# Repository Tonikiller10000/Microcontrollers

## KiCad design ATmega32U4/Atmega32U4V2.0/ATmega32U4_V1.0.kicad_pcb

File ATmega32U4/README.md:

# ATmega32U4

### Description:
This is an arduino micro development board with the ATmega32U4 microcontroller witch has integrated USB comunication protocol and don\`t need an external FTDI programmer.
This protothype can be used as an keyboard or an Keystroke injection tool because of it\`s integrated USB comunication protocol witch can very easely be used with the Keyboard.h library in the arduino IDE.

<table>
  <tr>
    <td></td>
    <td></td>
    <td></td>
  </tr>
 </table>

> [!IMPORTANT]
> The board need further testing and documentation. 

Links:
- ATmega32U4 datasheet: https://ww1.microchip.com/downloads/en/DeviceDoc/doc7799.pdf
- Results: https://github.com/Tonikiller10000/ATmega32U4/blob/main/Atmega32u4_Pictures/4.png
- Schematic1: https://static5.arrow.com/pdfs/2013/10/14/2/49/47/170/arduin_/manual/24arduino-micro-schematic.pdf
- Schematic2: https://cdn.sparkfun.com/datasheets/Dev/Arduino/Boards/Pro_Micro_v13b.pdf
- forum: https://forum.arduino.cc/t/my-first-atmega32u4-schematic/886582/3
- helping document: https://cdn-learn.adafruit.com/downloads/pdf/atmega32u4-breakout.pdf
- GitHub: https://github.com/adafruit/Adafruit_Atmega32u4_Breakout_Board

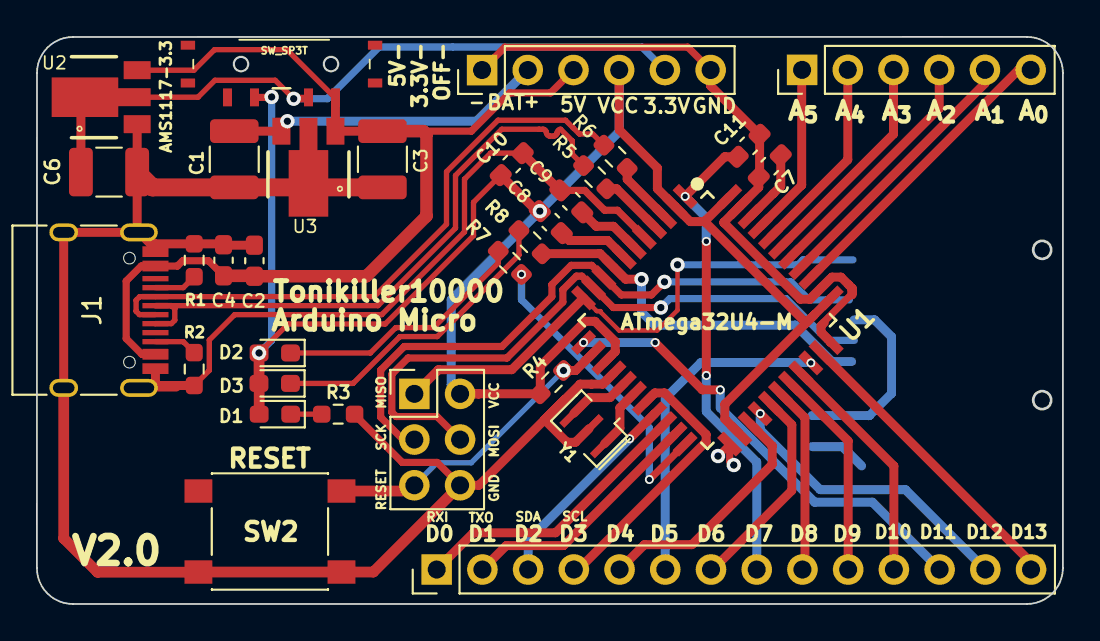
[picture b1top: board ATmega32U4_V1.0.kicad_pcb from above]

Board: 2 copper layers, 57.0 x 31.5 mm, 33 parts (1 on the bottom side), 45 nets.

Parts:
C1, C3: 100uF; C_1210_3225Metric_Pad1.33x2.70mm_HandSolder
C2, C7, C11: 0.1uF; C_0603_1608Metric_Pad1.08x0.95mm_HandSolder
C4: 10uF; C_0603_1608Metric_Pad1.08x0.95mm_HandSolder
C6: 10uF; C_1210_3225Metric_Pad1.33x2.70mm_HandSolder
C8, C9, C10: 1uF; C_0603_1608Metric_Pad1.08x0.95mm_HandSolder
C12: 0.1u; C_0603_1608Metric_Pad1.08x0.95mm_HandSolder
D1: POW; LED_0603_1608Metric_Pad1.05x0.95mm_HandSolder
D2: RX_LED; LED_0603_1608Metric_Pad1.05x0.95mm_HandSolder
D3: TX_LED; LED_0603_1608Metric_Pad1.05x0.95mm_HandSolder
J1: USB-C; USB_C_Receptacle_HRO_TYPE-C-31-M-12
J4: Conn_01x14; PinHeader_1x14_P2.54mm_Vertical
J5: ICSP; PinHeader_2x03_P2.54mm_Vertical
J6, J7: Conn_01x06; PinHeader_1x06_P2.54mm_Vertical
R1, R2: 5K1; R_0603_1608Metric_Pad0.98x0.95mm_HandSolder
R3: 1K; R_0603_1608Metric_Pad0.98x0.95mm_HandSolder
R4: 10K; R_0603_1608Metric_Pad0.98x0.95mm_HandSolder
R5, R6: 22R; R_0603_1608Metric_Pad0.98x0.95mm_HandSolder
R7, R8: 330R; R_0603_1608Metric_Pad0.98x0.95mm_HandSolder
SW1: SW_SP3T; MSK12C02
SW2: RESET; SW_Push_1P1T_NO_6x6mm_H9.5mm
U1: ATmega32U4-M; ATmega32U4
U2: AMS1117-3.3; PK(R-PSSO-F3)
U3: LM78L05_TO92; PK(R-PSSO-F3)
Y1: 16MHz; Resonator_SMD_Murata_CSTxExxV-3Pin_3.0x1.1mm

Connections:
+3.3V: C6.1, J6.5, SW1.2, U2.2 (VO)
A0: J7.6, U1.36 (PF7)
A1: J7.5, U1.37 (PF6)
A2: J7.4, U1.38 (PF5)
A3: J7.3, U1.39 (PF4)
A4: J7.2, U1.40 (PF1)
A5: J7.1, U1.41 (PF0)
D0/RXI: J4.1, U1.20 (PD2)
D1/TXO: J4.2, U1.21 (PD3)
D2: J4.3, U1.19 (PD1)
D3: J4.4, U1.18 (PD0)
D4: J4.5, U1.25 (PD4)
D5: J4.6, U1.31 (PC6)
D6: J4.7, U1.27 (PD7)
D7: C11.2, J4.8, U1.1 (PE6)
D8: J4.9, U1.28 (PB4)
D9: J4.10, U1.29 (PB5)
D10: J4.11, U1.30 (PB6)
D11: J4.12, U1.12 (PB7)
D12: J4.13, U1.26 (PD6)
D13: J4.14, U1.32 (PC7)
D+: J1.A6 (D+), J1.B6 (D+), R5.2
D-: J1.A7 (D-), J1.B7 (D-), R6.2
GND: C1.2, C2.2, C3.2, C4.2, C6.2, C7.1, C9.1, C10.1, C11.1, C12.2, J1.A1 (GND), J1.B1 (GND), J1.S1 (SHIELD), J5.6, J6.1, J6.6, R1.2, R2.2, R3.1, SW2.1, U1.5 (UGND), U1.15 (GND), U1.23 (GND), U1.33 (~HWB/PE2), U1.35 (GND), U1.43 (GND), U2.1 (GND), U3.2 (GND), Y1.2
MISO: J5.1, U1.11 (PB3)
MOSI: J5.4, U1.10 (PB2)
unnamed: D1.1 (K), R3.2
unnamed: D2.1 (K), R7.1
unnamed: D3.1 (K), R8.1
unnamed: J1.A5 (CC1), R1.1
unnamed: J1.B5 (CC2), R2.1
unnamed: C7.2, U1.42 (AREF)
unnamed: R5.1, U1.4 (D+)
unnamed: R6.1, U1.3 (D-)
unnamed: R7.2, U1.22 (PD5)
unnamed: C9.2, U1.6 (UCAP)
unnamed: C8.1, U1.7 (VBUS)
unnamed: U1.17 (XTAL1), Y1.1
unnamed: U1.16 (XTAL2), Y1.3
RESET: J5.5, R4.2, SW2.2, U1.13 (~RESET)
SCK: J5.3, U1.9 (PB1)
SD_CS: R8.2, U1.8 (PB0)
VBUS: C2.1, C3.1, C4.1, J1.A4 (VBUS), J1.B4 (VBUS), J6.3, SW1.1, U2.3 (VI), U3.1 (VO)
VCC: C8.2, C10.2, D1.2 (A), D2.2 (A), D3.2 (A), J5.2, J6.4, R4.1, SW1.3, U1.2 (UVCC), U1.14 (VCC), U1.24 (AVCC), U1.34 (VCC), U1.44 (AVCC)
VIN: C1.1, J6.2, U3.3 (VI)

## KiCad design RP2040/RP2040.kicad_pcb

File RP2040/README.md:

# RP2040

### Description:
This is an development board around the RP2040 microcontroller.

<table>
  <tr>
    <td></td>
    <td></td>
    <td></td>
  </tr>
 </table>

Links:
- raspberrypi website: https://www.raspberrypi.com/documentation/
- adafruit version: https://learn.adafruit.com/adafruit-feather-rp2040-pico/downloads
- digikey version: https://www.digikey.com/en/maker/projects/hardware-design-with-the-rp2040-part-1-schematic/c4326f0fd813413698d617cf625125ee
- technoblogy version: http://www.technoblogy.com/show?3U75
- RP2040 full datasheet: https://datasheets.raspberrypi.com/rp2040/rp2040-datasheet.pdf
- RP2040 hardware design: https://datasheets.raspberrypi.com/rp2040/hardware-design-with-rp2040.pdf?_gl=1*1qbzz4m*_ga*ODUyNTU5NTE1LjE3MTA2OTc5NzM.*_ga_22FD70LWDS*MTcxMDY5ODIzOC4xLjAuMTcxMDY5ODIzOC4wLjAuMA..
- RP2040 overview: https://blog.mbedded.ninja/programming/microcontrollers/raspberry-pi/rp2040/
- RP2040 Brief: https://datasheets.raspberrypi.com/rp2040/rp2040-product-brief.pdf?_gl=1*1qbzz4m*_ga*ODUyNTU5NTE1LjE3MTA2OTc5NzM.*_ga_22FD70LWDS*MTcxMDY5ODIzOC4xLjAuMTcxMDY5ODIzOC4wLjAuMA..
- RP2040 Guige: https://github.com/Sleepdealr/RP2040-designguide/blob/main/PCB/RP2040-Guide.pdf
- Connecting to the Internet with Raspberry Pi Pico W: https://datasheets.raspberrypi.com/picow/connecting-to-the-internet-with-pico-w.pdf?_gl=1*8x9u4j*_ga*ODUyNTU5NTE1LjE3MTA2OTc5NzM.*_ga_22FD70LWDS*MTcxMDY5ODIzOC4xLjEuMTcxMDY5ODI5OC4wLjAuMA..
- evaluation board: https://www.youtube.com/redirect?event=video_description&redir_token=QUFFLUhqbVFFMU1ZQk1fUEp6ZXZ1RmtYUzByZmJ3MTdOQXxBQ3Jtc0tubmhEVU5rYnc4cmx6YV9faG82OUE1akJoVXFMMjdjV3lXSnJnMk91R2VXVllvakZfVXg5QWZMQ181QUtDMzhUTUFTWnd3OGh4M2hGbkRnNXB1M2E2TFFfdThyanBOXzE4YWlFNy1aUmJERnJWUV9ZVQ&q=https%3A%2F%2Fwww.microtype.io%2Frp2040-eval-board%2F&v=ff8G8ZPj5cQ
- MicroTypeEngeneering video part3/3: https://www.youtube.com/watch?v=ff8G8ZPj5cQ
- Phil's Lab Hardware design video: https://www.youtube.com/watch?v=X00Cm5LMNQk&t=181s
- Raspberry Pi Pico W Datasheet: https://datasheets.raspberrypi.com/picow/pico-w-datasheet.pdf?_gl=1*8x9u4j*_ga*ODUyNTU5NTE1LjE3MTA2OTc5NzM.*_ga_22FD70LWDS*MTcxMDY5ODIzOC4xLjEuMTcxMDY5ODI5OC4wLjAuMA..

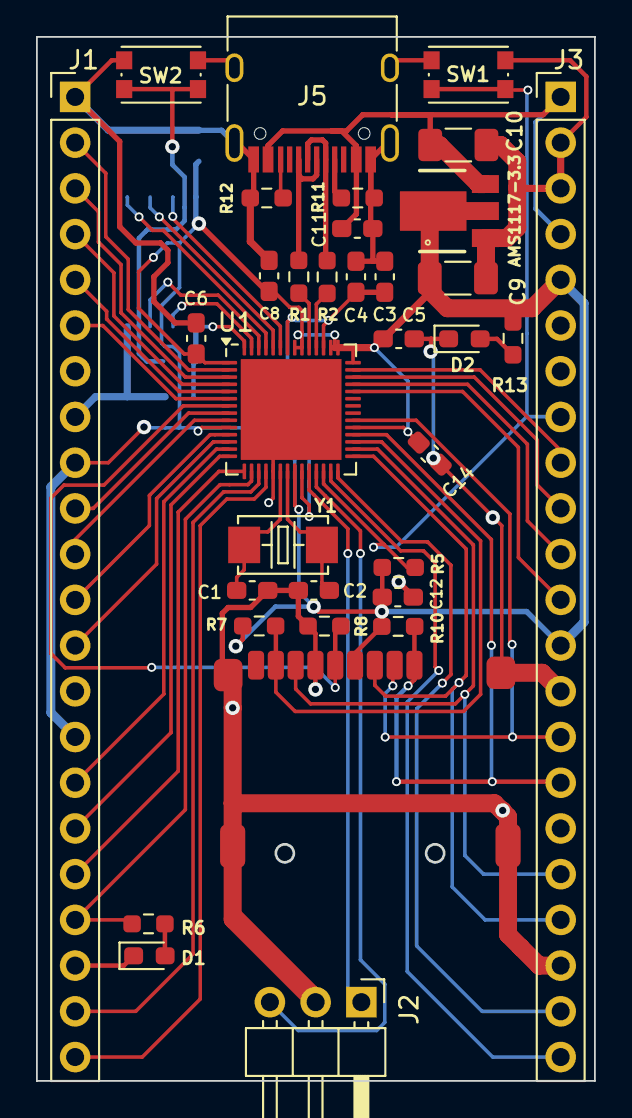
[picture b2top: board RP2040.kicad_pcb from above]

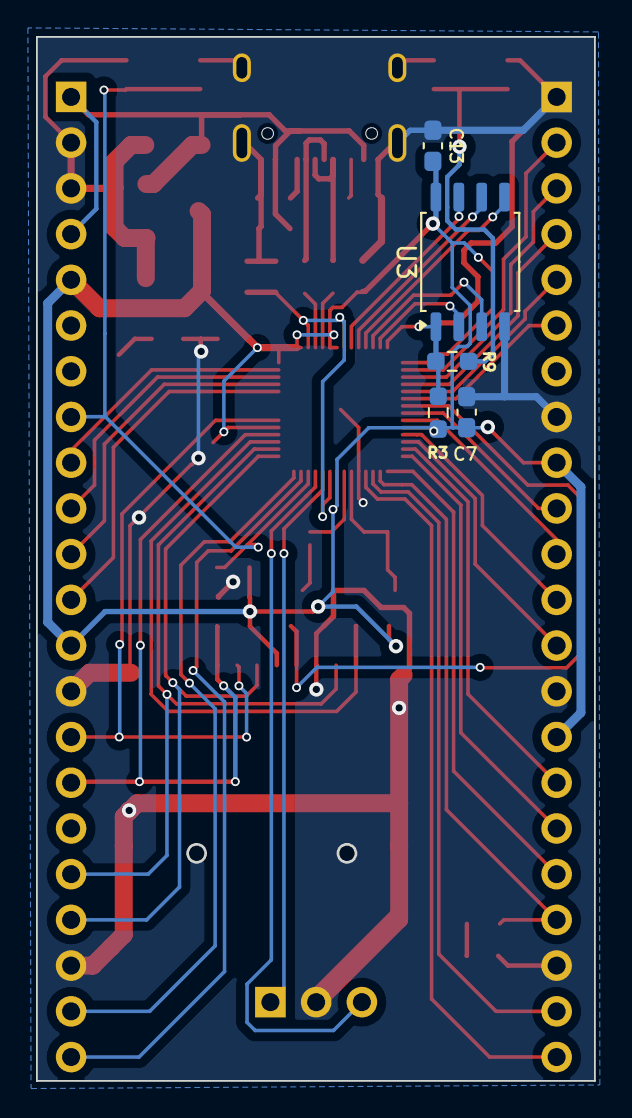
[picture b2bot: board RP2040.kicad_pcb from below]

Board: 2 copper layers, 30.9 x 58.0 mm, 38 parts (5 on the bottom side), 51 nets.

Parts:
C1, C2: 22pF; C_0603_1608Metric_Pad1.08x0.95mm_HandSolder
C3, C5: 1uF; C_0603_1608Metric_Pad1.08x0.95mm_HandSolder
C4, C6, C7, C8, C13, C14: 0.1uF; C_0603_1608Metric_Pad1.08x0.95mm_HandSolder
C9, C10: 10uF; C_1206_3216Metric_Pad1.33x1.80mm_HandSolder
C11, C12: 10uF; C_0603_1608Metric_Pad1.08x0.95mm_HandSolder
D1: BLINK; LED_0603_1608Metric_Pad1.05x0.95mm_HandSolder
D2: POW; LED_0603_1608Metric_Pad1.05x0.95mm_HandSolder
J1, J3: Conn_01x22; PinHeader_1x22_P2.54mm_Vertical
J2: Conn_01x03; PinHeader_1x03_P2.54mm_Horizontal
J5: USB-C_USB2.0; USB_C_Receptacle_HRO_TYPE-C-31-M-12
R1, R2: 27R; R_0603_1608Metric_Pad0.98x0.95mm_HandSolder
R3, R5, R6, R7, R10, R13: 10K; R_0603_1608Metric_Pad0.98x0.95mm_HandSolder
R8: DNP; R_0603_1608Metric_Pad0.98x0.95mm_HandSolder
R9: 1K; R_0603_1608Metric_Pad0.98x0.95mm_HandSolder
R11, R12: 5K1; R_0603_1608Metric_Pad0.98x0.95mm_HandSolder
SW1: RESET; SW_Push_1P1T_NO_CK_KMR2
SW2: BOOT; SW_Push_1P1T_NO_CK_KMR2
U1: RP2040; QFN-56-1EP_7x7mm_P0.4mm_EP5.6x5.6mm
U2: AMS1117-3.3; PK(R-PSSO-F3)
U3: W25Q128JVS; SOIC-8_5.23x5.23mm_P1.27mm
Y1: 12MHz; X2-SMD-5.0X3.2X1.3MM

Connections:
+1V2: C3.2, C4.2, U1.23 (DVDD), U1.45 (VREG_VOUT), U1.50 (DVDD)
+3.3V: C5.2, C6.2, C7.2, C8.2, C9.1, C12.1, C13.2, C14.2, J1.9, J1.15, J3.5, J3.13, R3.2, R5.2, R7.2, R10.2, R13.2, U1.1 (IOVDD), U1.10 (IOVDD), U1.22 (IOVDD), U1.33 (IOVDD), U1.42 (IOVDD), U1.43 (ADC_AVDD), U1.44 (VREG_IN), U1.48 (USB_VDD), U1.49 (IOVDD), U2.2 (VO), U3.8 (VCC)
ADC0: J3.12, U1.38 (GPIO26_ADC0)
ADC1: J3.11, U1.39 (GPIO27_ADC1)
ADC2: J3.10, U1.40 (GPIO28_ADC2)
ADC3: J3.9, U1.41 (GPIO29_ADC3)
D+: J5.A6 (D+), J5.B6 (D+), R1.2
D-: J5.A7 (D-), J5.B7 (D-), R2.2
GND: C1.1, C2.1, C3.1, C4.1, C5.1, C6.1, C7.1, C8.1, C9.2, C10.2, C11.2, C12.2, C13.1, C14.1, D1.1 (K), D2.1 (K), J1.1, J1.8, J1.14, J1.20, J2.2, J3.2, J3.3, J3.14, J3.20, J5.A1 (GND), J5.B1 (GND), J5.S1 (SHIELD), R8.2, R11.2, R12.2, SW1.1, SW2.2, U1.19 (TESTEN), U1.57 (GND), U2.1 (GND), U3.4 (GND)
GPIO4: J1.6, U1.6 (GPIO4)
GPIO6: J1.10, U1.8 (GPIO6)
GPIO7: J1.11, U1.9 (GPIO7)
GPIO8: J1.12, U1.11 (GPIO8)
GPIO9: J1.13, U1.12 (GPIO9)
GPIO10: J1.16, U1.13 (GPIO10)
GPIO11: J1.17, U1.14 (GPIO11)
GPIO12: J1.18, U1.15 (GPIO12)
GPIO13: J1.19, R6.1, U1.16 (GPIO13)
GPIO14: J1.21, U1.17 (GPIO14)
GPIO15: J1.22, U1.18 (GPIO15)
GPIO16: J3.22, U1.27 (GPIO16)
GPIO17: J3.21, U1.28 (GPIO17)
MOSI: J3.18, U1.30 (GPIO19)
unnamed: D1.2 (A), R6.2
unnamed: D2.2 (A), R13.1
unnamed: J5.A5 (CC1), R11.1
unnamed: J5.B5 (CC2), R12.1
unnamed: R9.1, SW2.1
unnamed: R2.1, U1.46 (USB_DM)
unnamed: R1.1, U1.47 (USB_DP)
unnamed: C1.2, U1.20 (XIN), Y1.1
unnamed: C2.2, U1.21 (XOUT), Y1.2
RESET: J3.8, R5.1, SW1.2, U1.26 (RUN)
RX: J1.3, U1.3 (GPIO1)
SCK: J3.19, U1.29 (GPIO18)
SCL: J1.5, U1.5 (GPIO3)
SD0: U1.53 (QSPI_SD0), U3.5 (DI(IO0))
SD1: U1.55 (QSPI_SD1), U3.2 (DO(IO1))
SD2: U1.54 (QSPI_SD2), U3.3 (IO2)
SD3: U1.51 (QSPI_SD3), U3.7 (IO3)
SDA: J1.4, U1.4 (GPIO2)
SD_CLK: R8.1, U1.7 (GPIO5)
SD_CS: R3.1, R9.2, U1.56 (QSPI_SS), U3.1 (~CS)
SD_D1: R7.1, U1.31 (GPIO20)
SD_D2: J3.16, R10.1, U1.32 (GPIO21)
SD_D3: J3.15, U1.34 (GPIO22)
SD_SCK: U1.52 (QSPI_SCLK), U3.6 (CLK)
SWDCLK: J2.1, U1.24 (SWCLK)
SWDDIO: J2.3, U1.25 (SWD)
TX: J1.2, U1.2 (GPIO0)
VBUS: C10.1, C11.1, J3.1, J3.4, J5.A4 (VBUS), J5.B4 (VBUS), U2.3 (VI)

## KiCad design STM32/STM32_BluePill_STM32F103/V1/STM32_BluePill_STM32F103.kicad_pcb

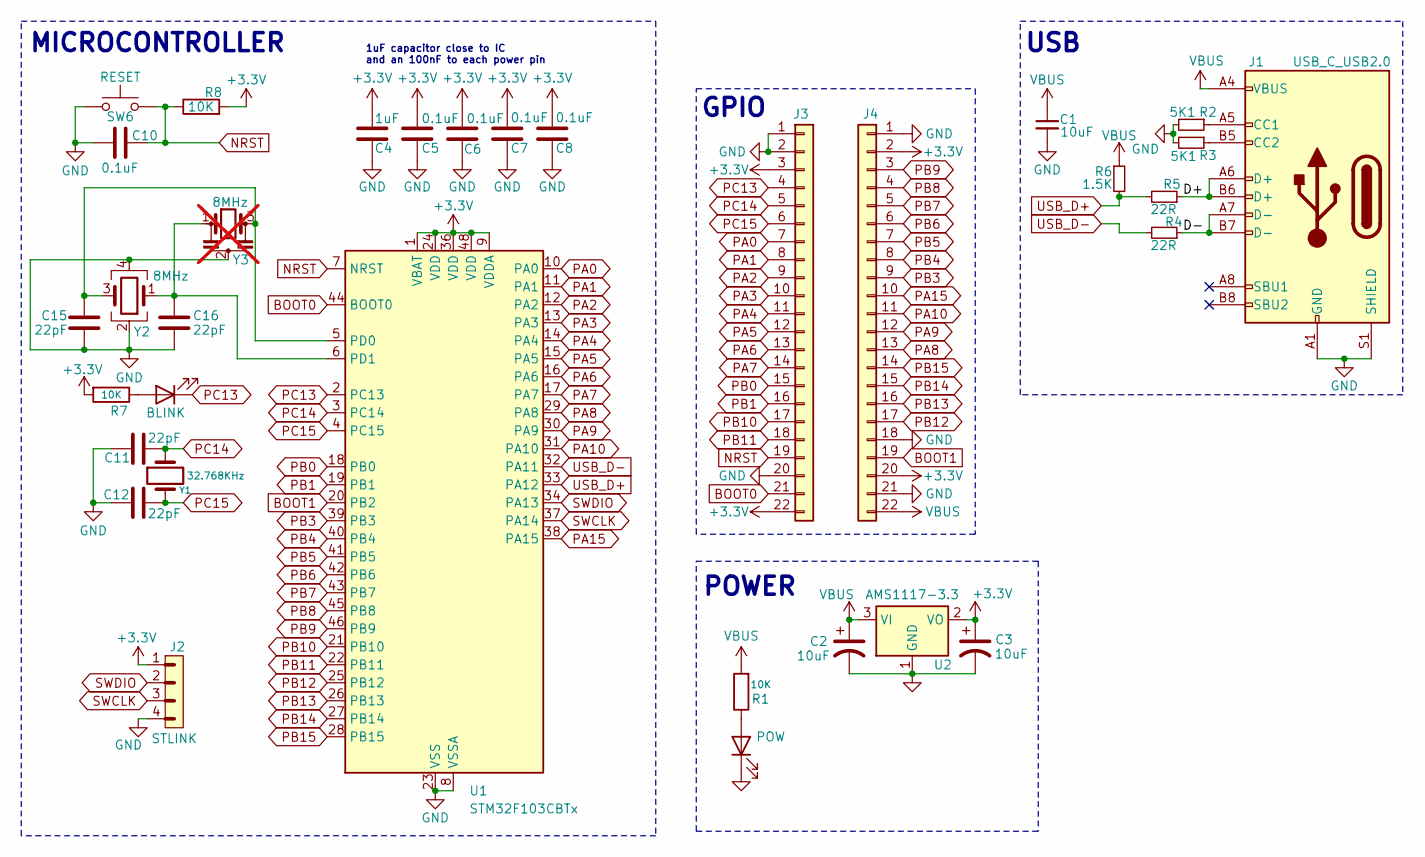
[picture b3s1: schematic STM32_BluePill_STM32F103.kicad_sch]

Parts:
C1: 10uF; C_0603_1608Metric
C2, C3: 10uF; C_1210_3225Metric_Pad1.33x2.70mm_HandSolder
C4: 1uF
C5, C6, C7, C8, C10: 0.1uF
C11, C12, C15, C16: 22pF
D1: POW
D2: BLINK
J1: USB_C_USB2.0
J2: STLINK; PinHeader_1x04_P2.54mm_Horizontal
J3, J4: Conn_01x22
R1, R7, R8: 10K; R_1206_3216Metric
R2, R3: 5K1; R_0603_1608Metric
R4, R5: 22R; R_0603_1608Metric
R6: 1.5K; R_0603_1608Metric
SW6: RESET
U1: STM32F103CBTx; LQFP-48_7x7mm_P0.5mm
U2: AMS1117-3.3; SOT-223-3_TabPin2
Y1: 32.768KHz
Y2: 8MHz
Y3: 8MHz; not fitted

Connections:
+3.3V: C3.1, C4.2, C5.2, C6.2, C7.2, C8.2, J2.1, J3.3, J3.22, J4.2, J4.20, R7.2, R8.2, U1.1 (VBAT), U1.9 (VDDA), U1.24 (VDD), U1.36 (VDD), U1.48 (VDD), U2.2 (VO)
/D+: J1.A6 (D+), J1.B6 (D+), R5.1
/D-: J1.A7 (D-), J1.B7 (D-), R4.1
BOOT0: J3.21, U1.44 (BOOT0)
BOOT1: J4.19, U1.20 (PB2)
GND: C1.2, C2.2, C3.2, C4.1, C5.1, C6.1, C7.1, C8.1, C10.2, C11.1, C12.1, C15.1, C16.1, D1.1 (K), J1.A1 (GND), J1.B1 (GND), J1.S1 (SHIELD), J2.4, J3.1, J3.2, J3.20, J4.1, J4.18, J4.21, R2.2, R3.2, SW6.1, U1.8 (VSSA), U1.23 (VSS), U1.35 (VSS), U1.47 (VSS), U2.1 (GND), Y2.2, Y2.4, Y3.2
NRST: C10.1, J3.19, R8.1, SW6.2, U1.7 (NRST)
unnamed: D1.2 (A), R1.1
unnamed: D2.2 (A), R7.1
unnamed: J1.A5 (CC1), R2.1
unnamed: J1.B5 (CC2), R3.1
unnamed: C15.2, U1.5 (PD0), Y2.3, Y3.3
unnamed: C16.2, U1.6 (PD1), Y2.1, Y3.1
PA0: J3.7, U1.10 (PA0)
PA1: J3.8, U1.11 (PA1)
PA2: J3.9, U1.12 (PA2)
PA3: J3.10, U1.13 (PA3)
PA4: J3.11, U1.14 (PA4)
PA5: J3.12, U1.15 (PA5)
PA6: J3.13, U1.16 (PA6)
PA7: J3.14, U1.17 (PA7)
PA8: J4.13, U1.29 (PA8)
PA9: J4.12, U1.30 (PA9)
PA10: J4.11, U1.31 (PA10)
PA15: J4.10, U1.38 (PA15)
PB0: J3.15, U1.18 (PB0)
PB1: J3.16, U1.19 (PB1)
PB3: J4.9, U1.39 (PB3)
PB4: J4.8, U1.40 (PB4)
PB5: J4.7, U1.41 (PB5)
PB6: J4.6, U1.42 (PB6)
PB7: J4.5, U1.43 (PB7)
PB8: J4.4, U1.45 (PB8)
PB9: J4.3, U1.46 (PB9)
PB10: J3.17, U1.21 (PB10)
PB11: J3.18, U1.22 (PB11)
PB12: J4.17, U1.25 (PB12)
PB13: J4.16, U1.26 (PB13)
PB14: J4.15, U1.27 (PB14)
PB15: J4.14, U1.28 (PB15)
PC13: D2.1 (K), J3.4, U1.2 (PC13)
PC14: C11.2, J3.5, U1.3 (PC14), Y1.1
PC15: C12.2, J3.6, U1.4 (PC15), Y1.2
SWCLK: J2.3, U1.37 (PA14)
SWDIO: J2.2, U1.34 (PA13)
USB_D+: R5.2, R6.2, U1.33 (PA12)
USB_D-: R4.2, U1.32 (PA11)
VBUS: C1.1, C2.1, J1.A4 (VBUS), J1.B4 (VBUS), J4.22, R1.2, R6.1, U2.3 (VI)

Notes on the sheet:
1uF capacitor close to IC and an 100nF to each power pin
USB
POWER
MICROCONTROLLER
GPIO

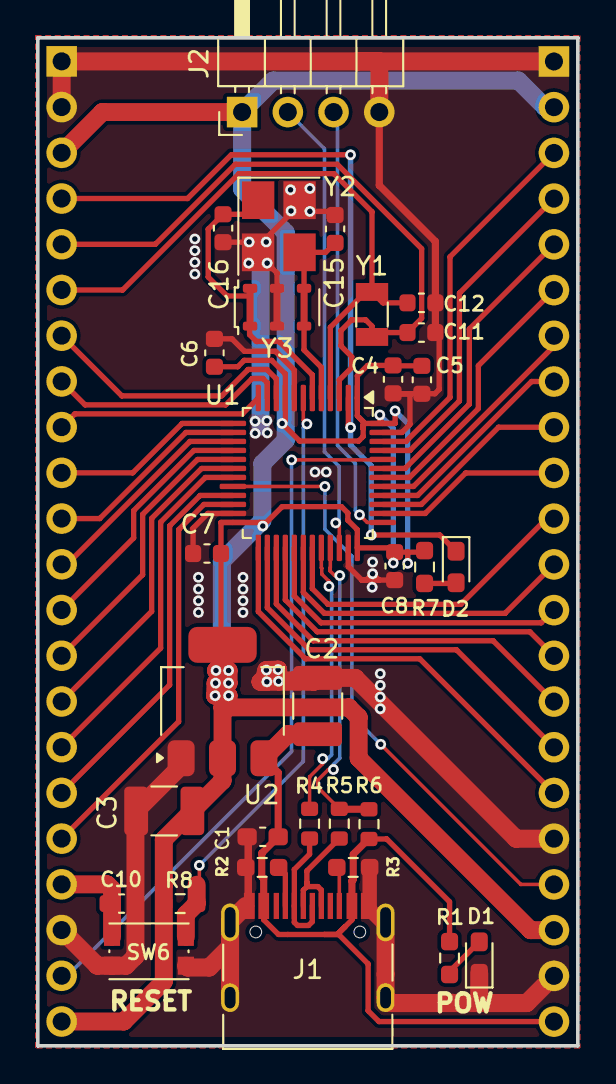
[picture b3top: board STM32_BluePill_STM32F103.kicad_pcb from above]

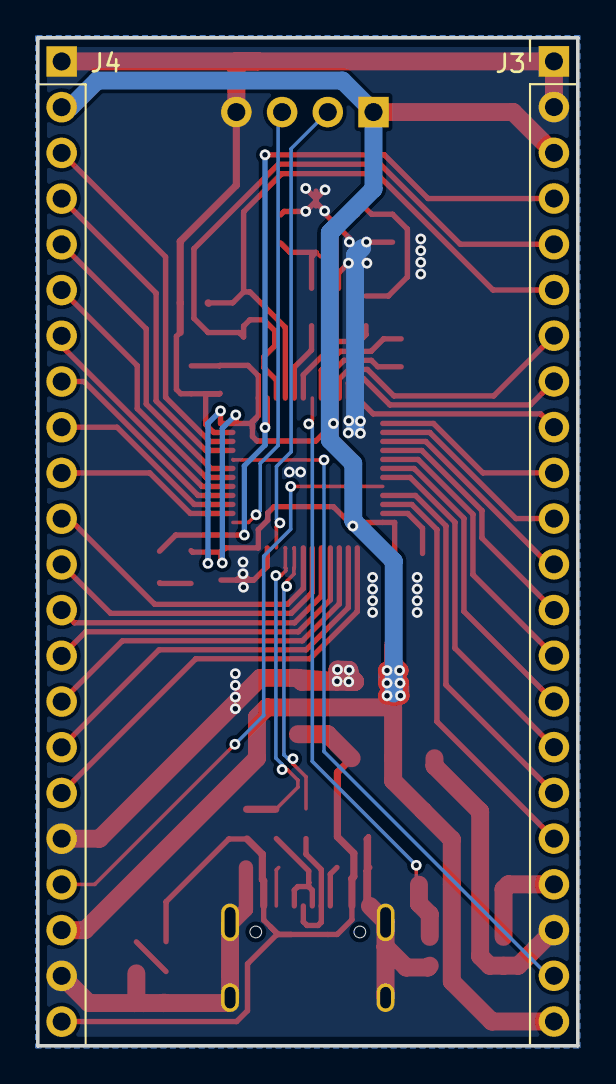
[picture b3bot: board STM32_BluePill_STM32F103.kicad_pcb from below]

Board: 2 copper layers, 30.0 x 56.0 mm, 33 parts (2 on the bottom side), 48 nets.
